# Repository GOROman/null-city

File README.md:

# NULL CITY NC-03

Bambu H3Cで製作する、交換式天板の6ボタンアーケードスティック。白い面取りケースに、NULL FONTのロゴとネイビー・マゼンタのデカールを組み合わせています。写真は2026-11-16の実機です。

**[ブラウザーで3Dプレビュー ↗](https://goroman.github.io/null-city/)** · [制作日記・設計記録](docs/development-diary.md) · [部品表](BOM.md)

## 仕様と構成

| 項目 | 内容 |
|---|---|
| 外形 | 公称300 × 190 mm、脚込み高さ約55 mm（レバー・ボタンを除く） |
| 筐体 | 下ケース・上フレーム・交換式天板。天板288 × 178 × 4 mm |
| レバー | セイミツ製のゲーセンバッグ実物に合わせた直接固定。40 × 40 mmピッチ、逃げ穴φ4.5 mm × 4 |
| ボタン | Blast City 1Pの6ボタン配列。メインφ30 × 6（緑3・透明3）、1P／STARTはφ24 |
| 表示LED | レバー8方向＋各ボタン、計16個の4 × 4 mm角窓。裏面にWS2812互換モジュール用受け座 |
| 筐体照明 | 前面・左右のLED収容溝と別体の乳白カバー |
| USB配線 | 背面ケーブル出口、外径4 mm想定のS字ガイドと押さえ |

実機写真で筐体・天板・操作部・デカールの組立を確認できます。レバーは試験片でねじ4本の固定と8方向動作を確認済み。通信、LED点灯、接続済み配線の干渉、耐久性は引き続き確認が必要です。写真だけで電気的な動作確認済みとはしていません。

## 製作データ

| 作りたいもの | データ・手順 |
|---|---|
| 本体一式 | [H3C用6プレート3MF](print/h3c/NC03_H3C_6plates_lighting_sliced.3mf) ／ [造形設定](PRINT_SETTINGS.md) |
| 天板 | [標準3MF](print/h3c/03_control_panel.3mf) ／ [時短試作3MF](print/h3c/03_control_panel_fast.3mf) |
| 表面マルチカラー天板 | [3MF](print/h3c/03_control_panel_multicolor_sliced.3mf) ／ [3色印刷・角LED窓の手順](print/h3c/PANEL_MULTICOLOR.md) |
| 下ケース・照明カバー | [下ケース時短3MF](print/h3c/01_lower_tray_fast.3mf) ／ [カバー3MF](print/h3c/06_light_diffusers.3mf) ／ [照明構成](LIGHTING.md) |
| デカール | [全4枚をA4一枚に配置したPDF](artwork/decal/NC03_all_decals_A4_versioned.pdf) ／ [印刷・Bambu Suiteカット手順](artwork/decal/README.md) |
| 部品の購入 | [機構BOM](BOM.md) ／ [CSV](BOM.csv) ／ [メーカー寸法図PDF](docs/references/README.md) |
| 嵌合確認 | [レバー取付・測定](docs/fit/README.md) ／ [照明試験片](print/lighting-fit/README.md) ／ [USBガイド試験片](print/usb-relief/README.md) |
| コントローラー基板 | [KiCad設計・回路図・電子部品BOM](hardware/nc03-controller/README.md) |
| NULL FONT | [フォントパッケージ](fonts/null-font/) ／ [ベクターロゴ](artwork/logo/null-city.svg) |

マルチカラー天板は凹ロゴの底面だけ白、`///`をマゼンタにする一体造形です。写真のデカール仕上げとは別の仕上げ方法で、3色印刷・LED保持は実物確認待ちです。

コントローラー基板はXIAO nRF52840 Plusを使うA0試作。USB／BLEの通信ファームウェア、Switch／PS互換性は未実装・未検証です。[基板の制約と対応範囲](hardware/nc03-controller/README.md)を確認してください。

## 3Dプリント

Bambu Studioの **H3C／0.4 mm Standard・Textured PEI Plate** を使用し、実際の材料と装着ノズルに合わせて再スライスします。

| 設定 | 本体の標準試作 | 同梱6プレート版の時短試作 |
|---|---|---|
| 積層／初層 | 0.20／0.20 mm | 0.28／0.20 mm |
| 壁 | 4周 | 3周 |
| 上面／底面 | 各5層 | 各4層 |
| 充填 | Gyroid 15% | Gyroid 10% |
| ブリム | 外周5 mm、隙間0.15 mm | 同左 |
| サポート | なし | なし |
| 外壁／天面 | 100／80 mm/s | 同左 |

PLAの開始値はノズル220℃、ベッド55℃、最大体積流量12 mm³/s。材料メーカーの指定を優先してください。脚は別プレートでTPU、カバーは半透明PLA。各専用ジョブの設定と見積は[PRINT_SETTINGS.md](PRINT_SETTINGS.md)を参照。

## デカールの印刷とカット

実機では天板・前面・左右の4枚を、[A4横一枚のベクターPDF](artwork/decal/NC03_all_decals_A4_versioned.pdf)から印刷しました。

- Canon XK130、A4写真用紙 光沢ゴールド（GL-101）、後トレイ、高品質・カラー・片面。
- 倍率100%、フチなしOFF、用紙に合わせるOFF。
- [Suite用カットデータ](artwork/decal/NC03_all_decals_A4_CUT_ONLY_NOMINAL.lac)は33穴＋4外周の計37閉輪郭。用紙を貼るたびにカメラで位置・角度を合わせます。
- 余白・塗り足しが必要な場合は[余白付きA4二枚版](artwork/decal/NC03_decals_A4_2sheets.pdf)を使用。

材料設定、刃、位置合わせと試し切りの注意点は[デカールREADME](artwork/decal/README.md)にまとめています。

## 設計図と3Dビューアー

[制作日記・設計記録](docs/development-diary.md)に、分解図・ワイヤーフレーム・照明構造・寸法・試作の経緯をまとめています。レンダリングの発光表現は完成イメージです。

[PBR Webビューアー](https://goroman.github.io/null-city/)では回転・ズーム・分解表示、HDR IBL、SSAO、露出・背景色、RGB LEDアニメーション、レバーとボタンの操作を試せます。[ローカル実行・GitHub Pages公開手順](web/README.md)。

## モデルと画像の再生成

`NULL_CITY_NC03.blend` が組立モデル、`NULL_CITY_NC03.py` が生成スクリプト、`STL/` が部品別の造形データです。リポジトリ直下で実行します。

```sh
blender --background --factory-startup --python-exit-code 1 --python NULL_CITY_NC03.py
python3 scripts/render_all.py
```

実機のトップ写真は `docs/images/nc03-built.jpg`。Blenderの再レンダリングでは更新されません。照明・デカールなどの生成手順は各リンク先を参照してください。

## ライセンス

Copyright © 2026 GOROman。適用範囲は[LICENSE](LICENSE)を参照。

| 対象 | ライセンス |
|---|---|
| スクリプト（フォントパッケージを除く） | [MIT](LICENSES/MIT.txt) |
| 造形・デカール・オリジナル画像・設計設定・ドキュメント | [CC BY 4.0](LICENSES/CC-BY-4.0.txt) |
| NULL FONT（字形ソース・生成スクリプトを含む） | [SIL OFL 1.1](fonts/null-font/OFL.txt) |

メーカー寸法図など第三者資料は、それぞれの権利・ライセンスに従います。

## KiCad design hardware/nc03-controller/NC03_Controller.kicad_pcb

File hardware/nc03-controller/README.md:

# NC-03 USB/BLE controller — KiCad A0

XIAO nRF52840 **Plus / non-Sense**を使う、NC-03用キャリア基板の試作設計です。**基板データは作成済み、実装・通信ファームウェア・実機互換性・ケース内取付は未検証**です。Switch/PSで動作する完成済みコントローラーではありません。

[KiCadプロジェクト](NC03_Controller.kicad_pro) / [回路図PDF](docs/schematic.pdf) / [基板表面](docs/board-top.svg) / [基板裏面](docs/board-bottom.svg) / [実装図](docs/assembly.svg) / [部品表CSV](BOM.csv) / [ピン割当](firmware/pinmap.csv) / [一次資料](docs/REFERENCES.md)

KiCadからの実データ描画。U1のXIAO本体は3Dモデル未収録のため描画されません。U1の29パッドと実装位置は基板図で確認できます。形状・配線の画像であり、通電写真ではありません。

## 現行天板のシリアルLED

新しい[四角窓・シリアルLED天板](../../print/h3c/PANEL_MULTICOLOR.md)では、16個のNeoPixel/WS2812互換モジュールと前面・側面ストリップをJ14から1本の直列チェーンで制御します。基板の配線変更は不要です。全ピクセルを含めてRGB電流予算150mAを分配します。A0のPCA9685・R41〜R56・J12/J13は旧単色構成用のオプションとなり、新LEDのDINには接続しません。

下表・回路図・基板BOMは旧単色ドライバーも搭載できるA0の共通回路を示します。現行天板でその部品は省略可能です。通信・LEDファームと新モジュール装着は未検証です。

## 構成

| 機能 | 回路・状態 |
|---|---|
| MCU | XIAO nRF52840 Plus、標準版/Senseは代用不可。Plus底面パッドも接合 |
| 主入力 | レバー4方向＋主6＋1P/STARTの12点をGPIO直結、330Ω＋1nF、外部10kプルアップ |
| 操作表示 | 既存の3mm単色LED16個、PCA9685PWで個別PWM、1kΩ抵抗で約2〜3mA/点 |
| 前面・左右RGB | 5VのWS2812系ストリップ用出力、3.3→5Vレベル変換、ストリップを直列に接続 |
| LED電源 | USB VBUS→350mA PTC→TPS22918。起動時OFF、USB設定完了後に予算内で有効化 |
| バッテリー | 保護回路付き1S LiPo、XIAO内蔵充電回路を利用。逆接保護・独立電源パスはキャリアに追加していない |
| モード | 外付けSPDT ON–OFF–ONでPC／PS外部変換器／Switch、別SPSTでUSB／BLE |
| USB | XIAOのType-Cを利用。キャリアに2個目のUSB端子やUSB信号配線は設けない |
| 拡張 | SWD、3.3V I²C。Home/Share/Touchpad等の補助入力基板は未設計 |
| 基板 | 110×85mm、2層、1.6mm想定、M3用φ3.2 NPTH×4、ピッチ100×75mm |

## 接続先と切り替え

| 選択 | 接続計画 | 実装状況 |
|---|---|---|
| PC＋USB | USB HIDゲームパッド、1msポーリング目標 | ハード回路のみ。ファーム未実装、遅延未測定 |
| PC＋BLE | HID over GATT、接続間隔7.5msを要求 | 同上。ホストによって実際の間隔が変わる |
| Switch＋USB | 初代Switch向けUSBプロトコル | ファーム未実装、実機未検証。Switch 2を含まない |
| PS＋USB | 対応する市販認証変換器へUSB接続 | 変換器・PS世代・USBプロファイルは選定/実機照合待ち。直結対応ではない |
| Switch/PS＋BLE | 対象外 | BLE搭載だけでは両コンソールの無線仕様に対応しない |

J10は**PC–PS/ADAPTER–SWITCH**の並びになる3位置スイッチです。共通GND、両端の信号を別々に読むので、中立OFF位置でも電源は落ちません。未接続はPS/ADAPTER位置になります。USB/BLEは別スイッチに分け、J11開放=USB、短絡=BLE。切り替え後は全入力解除→通信停止→USB再列挙またはBLE接続を行うファーム仕様です。[詳細](firmware/PROTOCOL.md)

PS4/PS5は認証のある対応変換器などが必要です。例としてBrookの公開資料を参照していますが、この自作デバイスは互換リストに載っておらず、変換器経由の動作も確認していません。USBの識別子だけでPS対応とはしません。PS世代の回答後に対象変換器を確定します。

## コネクター

全コネクターは上面実装のJST XH縦型2.50mm。**ピン番号は基板図の四角パッドを1番**として読む。一般的なLiPoのJST PHとは異なり、極性も共通規格と仮定しないこと。

| 端子 | ピン順 |
|---|---|
| J1 レバー | 1 GND、2 UP、3 DOWN、4 LEFT、5 RIGHT |
| J2〜J7 主ボタン | B1〜B6、各1 GND／2入力 |
| J8・J9 補助ボタン | 1P／START、各1 GND／2入力 |
| J10 プロファイル | 1 PC側、2共通GND、3 Switch側。SPDT ON–OFF–ON |
| J11 USB/BLE | 1選択入力、2 GND。開放USB、短絡BLE |
| J12 方向LED | 1 +5V_LED、2〜9はK0〜K7、共通アノード配線。方向は前面から0=右、以降反時計回り45°刻み |
| J13 ボタンLED | 1 +5V_LED、2〜9はK8〜K15、B1〜B6・1P・STARTの順 |
| J14 RGB | 1 +5V_LED、2 DIN、3 GND。ストリップの入力側へ |
| J15 電池 | 1保護済み電池＋、2電池−/GND。1S 3.7V公称／満充電4.2Vのみ |
| J16 電池スイッチ | 1電池＋、2 XIAO BAT＋。外付けSPSTで結ぶ。OFFでは電池を充電回路からも切り離す |
| J17 AUX | 1 3.3V、2 SDA、3 SCL、4 GND。5V機器用ではない |
| J18 SWD | 1 3.3V参照、2 SWDIO、3 SWDCLK、4 RESET、5 GND |

LS-55-01のハーネスの実際の方向・共通線は現物照合し、線色で決めない。GPIOへ5VやLED電源を接続しない。XIAO標準11 GPIOのキャリアとしては動作しない。

## 電源とケースへの組付け

USBと電池はXIAOの既存回路へ接続します。別の5V電源をJ14やVBUSへ注入しません。主電源はXIAO、キャリアの3.3Vは出力から受けるだけです。電池の保護回路・適切な充電設定は別途必要。J16をOFFにすると電池充電も止まります。

RGBの合計はソフトで150mAを初期上限にし、単色LED約50mA、MCU/無線、電池充電の最大電流を加えて実際に許可されたUSB電流を下回る必要があります。350mA PTCは精密な定電流制限ではありません。TPS22918の立ち上がりと47uFの充電突入は実測します。PCA9685の出力はリセット時LOWのため、全消灯を書いてからLED_ENABLEを上げます。電池駆動時は5V昇圧がないためLEDを消灯します。

USB Type-Cを外側に出す場合は、XIAOのUSB-Cにつながるデータ対応パネル延長部品をケースに固定します。**既存の背面8×6mm切り欠きはケーブル用であり、Type-Cメス端子のパネル固定穴ではありません。** 端子外形、CC/USB2.0配線とケーブル方向を現物照合したうえで、後から別ブラケット・開口を設計します。この変更で印刷中の下ケース/STL/3MFは変更していません。

基板のM3穴ピッチ100×75mmは独立した新設穴で、現行ケースのボスと一致しません。**ケースとの機械的適合は未完了**です。発注前に1:1基板図を印刷し、レバー本体・ボタン端子・ナット・USB S字ガイド・LED溝を避けて仮置きします。M3絶縁スペーサー等の取付台とType-C固定は次の機械設計。アンテナ側はcarrier銅箔禁止領域を確保しましたが、筐体内の金属レバー・配線・電池からの離隔とRF性能は実物評価が必要です。

## 検証と再生成

KiCad 10.0.8でERC、DRC、回路図とPCBのネット/フットプリント照合を実施。結果は[ERC](checks/ERC.rpt)／[DRC](checks/DRC.rpt)。配線済みデータが正本です。自動配線後に0.2mm未満のネック部分を0.2mmへ拡幅し、改めてDRCしています。

再生成は現在の基板配線を上書きします。通常の閲覧・編集は `NC03_Controller.kicad_pro` を開きます。生成スクリプトと詳細手順は[scripts/README.md](scripts/README.md)。

製造用Gerber/ドリルは含めていません。通信ファーム、PS変換器、ケース取付、充電電流・ESD・RF・遅延を確認してから製造リリースに進みます。ERC/DRC合格は、これらの実機検証の代わりにはなりません。

## 追加購入部品

[電子部品BOM](BOM.csv)は基板上89部品。ほかにXHハウジング/コンタクトとハーネス、外付けSPDT ON–OFF–ON×1、SPST×2（USB/BLEと電池）、データ対応USB-Cパネル延長、適切な保護付き1S電池、RGBストリップ、現行天板用の9.1mm角シリアルRGBモジュール16個（旧丸窓天板のみ3mm単色LED）、M3取付部品が必要です。XIAO本体はU1としてBOMに含みます。ストリップ長、電池サイズ、PS変換器は未確定です。

ソフトウェアはMIT。Seeedのランドパターンを組み込むPCB/回路図と派生出力はCC BY-SA 4.0。[出典・変更点・例外](vendor/README.md)。筐体・デカールのCC BY 4.0とNULL FONTのOFLは変更していません。

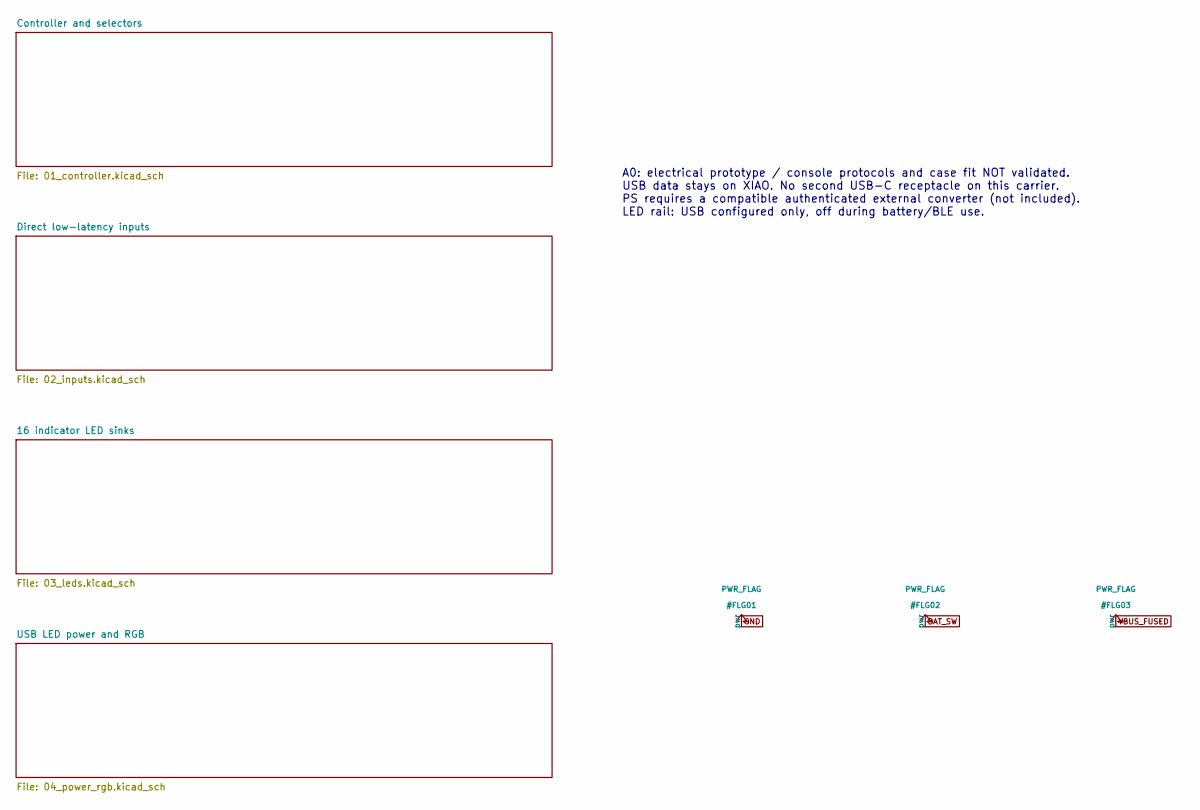
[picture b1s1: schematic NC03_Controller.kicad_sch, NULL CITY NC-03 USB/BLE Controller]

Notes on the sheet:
A0: electrical prototype / console protocols and case fit NOT validated. USB data stays on XIAO. No second USB-C receptacle on this carrier. PS requires a compatible authenticated external converter (not included). LED rail: USB configured only, off during battery/BLE use.

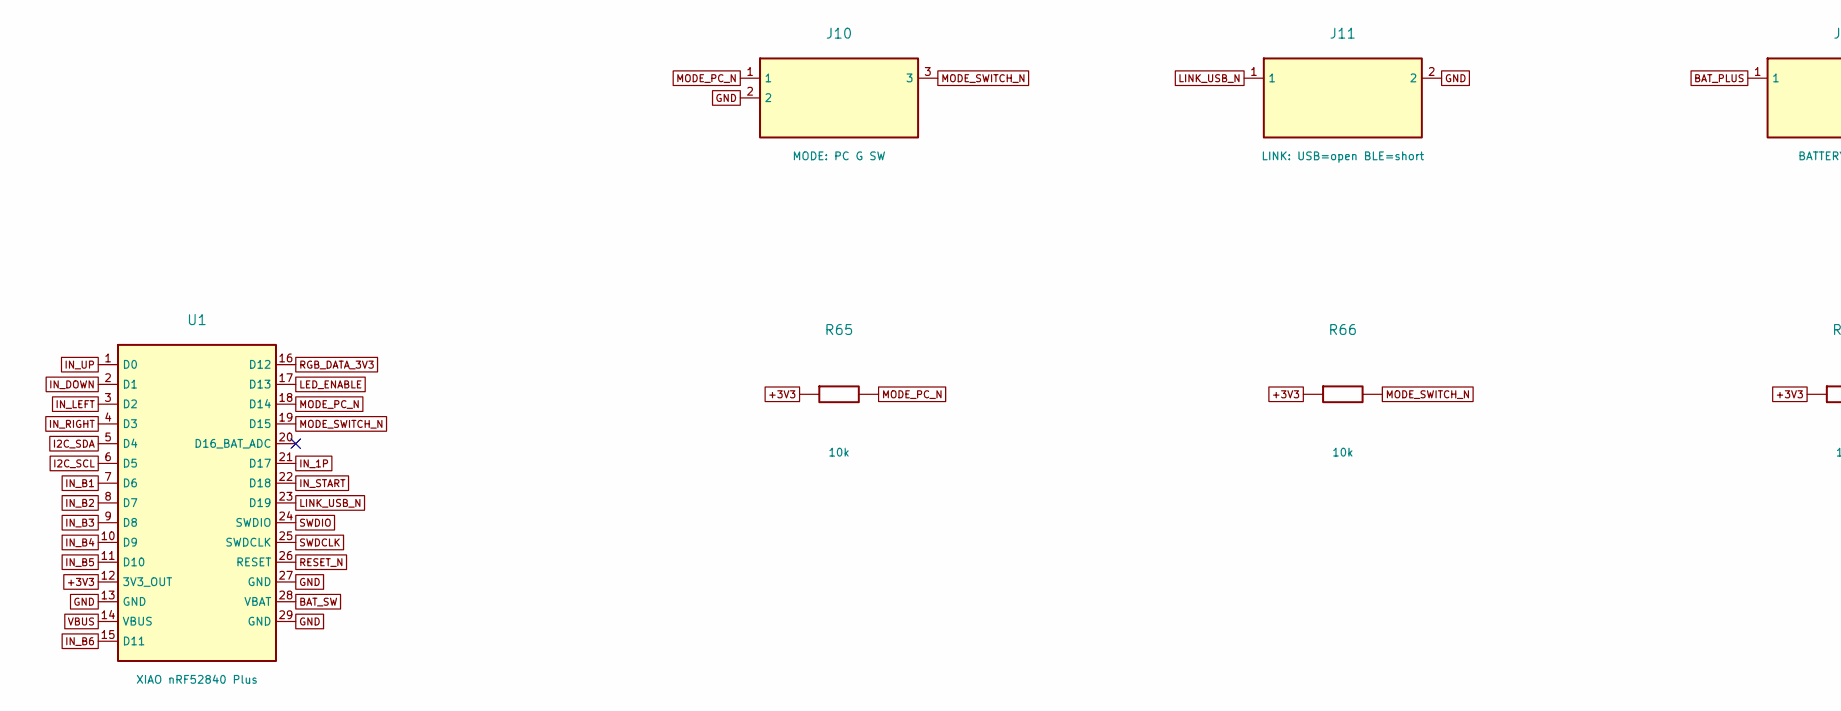
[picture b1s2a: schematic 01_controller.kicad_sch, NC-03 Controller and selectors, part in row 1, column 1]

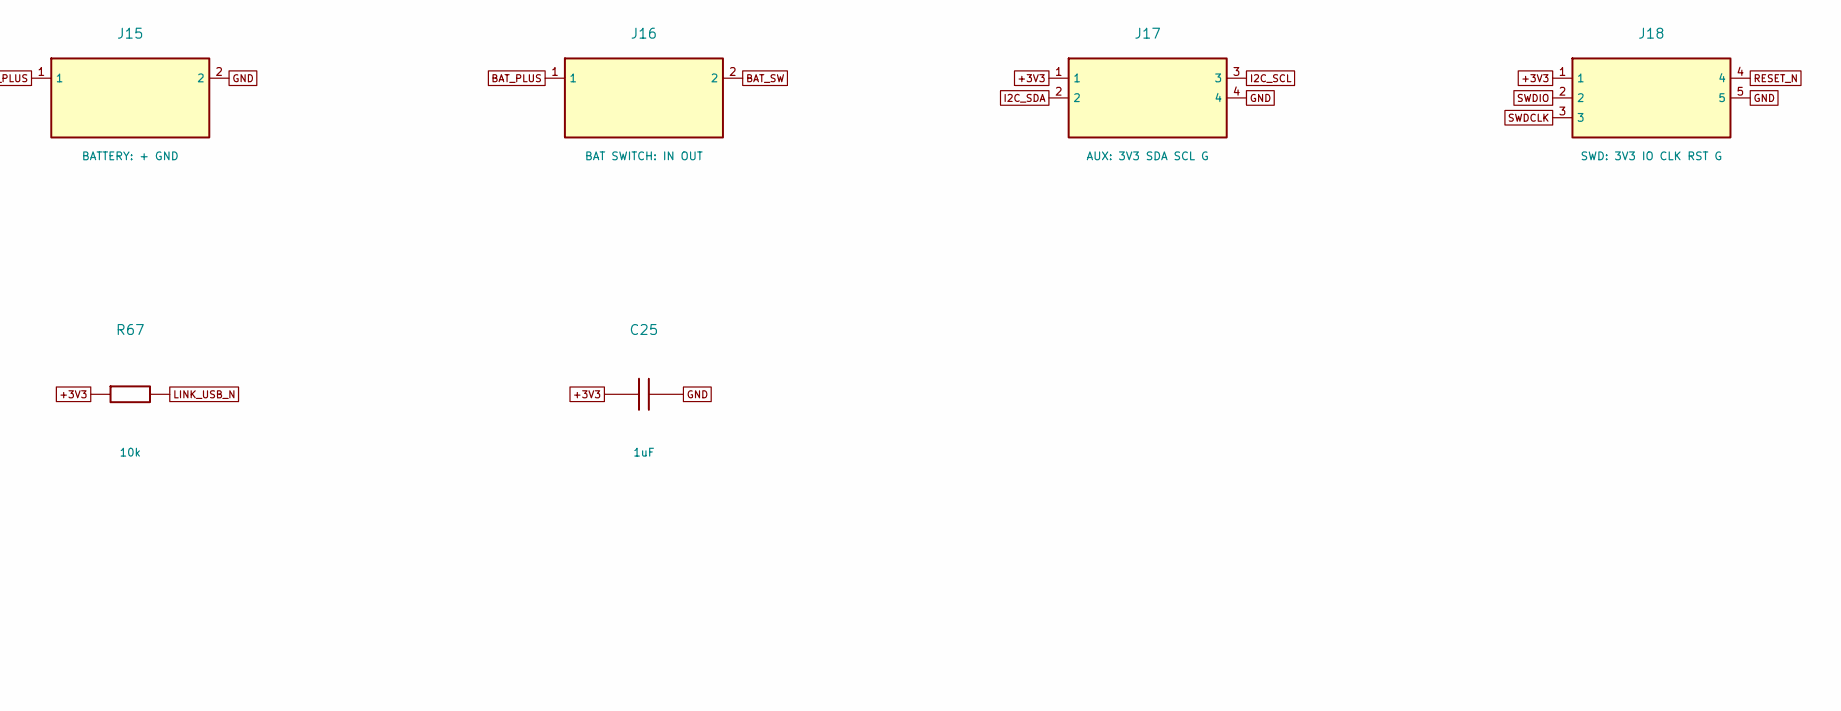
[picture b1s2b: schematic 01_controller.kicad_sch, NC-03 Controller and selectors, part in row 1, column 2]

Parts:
C25: 1uF; Capacitor_SMD_C_0805_2012Metric
J10: MODE: PC G SW; Connector_JST_JST_XH_B3B-XH-A_1x03_P2.50mm_Vertical
J11: LINK: USB=open BLE=short; Connector_JST_JST_XH_B2B-XH-A_1x02_P2.50mm_Vertical
J15: BATTERY: + GND; Connector_JST_JST_XH_B2B-XH-A_1x02_P2.50mm_Vertical
J16: BAT SWITCH: IN OUT; Connector_JST_JST_XH_B2B-XH-A_1x02_P2.50mm_Vertical
J17: AUX: 3V3 SDA SCL G; Connector_JST_JST_XH_B4B-XH-A_1x04_P2.50mm_Vertical
J18: SWD: 3V3 IO CLK RST G; Connector_JST_JST_XH_B5B-XH-A_1x05_P2.50mm_Vertical
R65, R66, R67: 10k; Resistor_SMD_R_0805_2012Metric
U1: XIAO nRF52840 Plus; XIAO_nRF52840_Plus

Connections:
+3V3: C25.1, J17.1, J18.1, R65.1, R66.1, R67.1, U1.12 (3V3_OUT); also elsewhere on the board
BAT_PLUS: J15.1, J16.1
BAT_SW: J16.2, U1.28 (VBAT)
GND: C25.2, J10.2, J11.2, J15.2, J17.4, J18.5, U1.13 (GND), U1.27 (GND), U1.29 (GND); also elsewhere on the board
I2C_SCL: J17.3, U1.6 (D5); also elsewhere on the board
I2C_SDA: J17.2, U1.5 (D4); also elsewhere on the board
IN_1P: U1.21 (D17); also elsewhere on the board
IN_B1: U1.7 (D6); also elsewhere on the board
IN_B2: U1.8 (D7); also elsewhere on the board
IN_B3: U1.9 (D8); also elsewhere on the board
IN_B4: U1.10 (D9); also elsewhere on the board
IN_B5: U1.11 (D10); also elsewhere on the board
IN_B6: U1.15 (D11); also elsewhere on the board
IN_DOWN: U1.2 (D1); also elsewhere on the board
IN_LEFT: U1.3 (D2); also elsewhere on the board
IN_RIGHT: U1.4 (D3); also elsewhere on the board
IN_START: U1.22 (D18); also elsewhere on the board
IN_UP: U1.1 (D0); also elsewhere on the board
LED_ENABLE: U1.17 (D13); also elsewhere on the board
LINK_USB_N: J11.1, R67.2, U1.23 (D19)
MODE_PC_N: J10.1, R65.2, U1.18 (D14)
MODE_SWITCH_N: J10.3, R66.2, U1.19 (D15)
RESET_N: J18.4, U1.26 (RESET)
RGB_DATA_3V3: U1.16 (D12); also elsewhere on the board
SWDCLK: J18.3, U1.25 (SWDCLK)
SWDIO: J18.2, U1.24 (SWDIO)
VBUS: U1.14 (VBUS); also elsewhere on the board

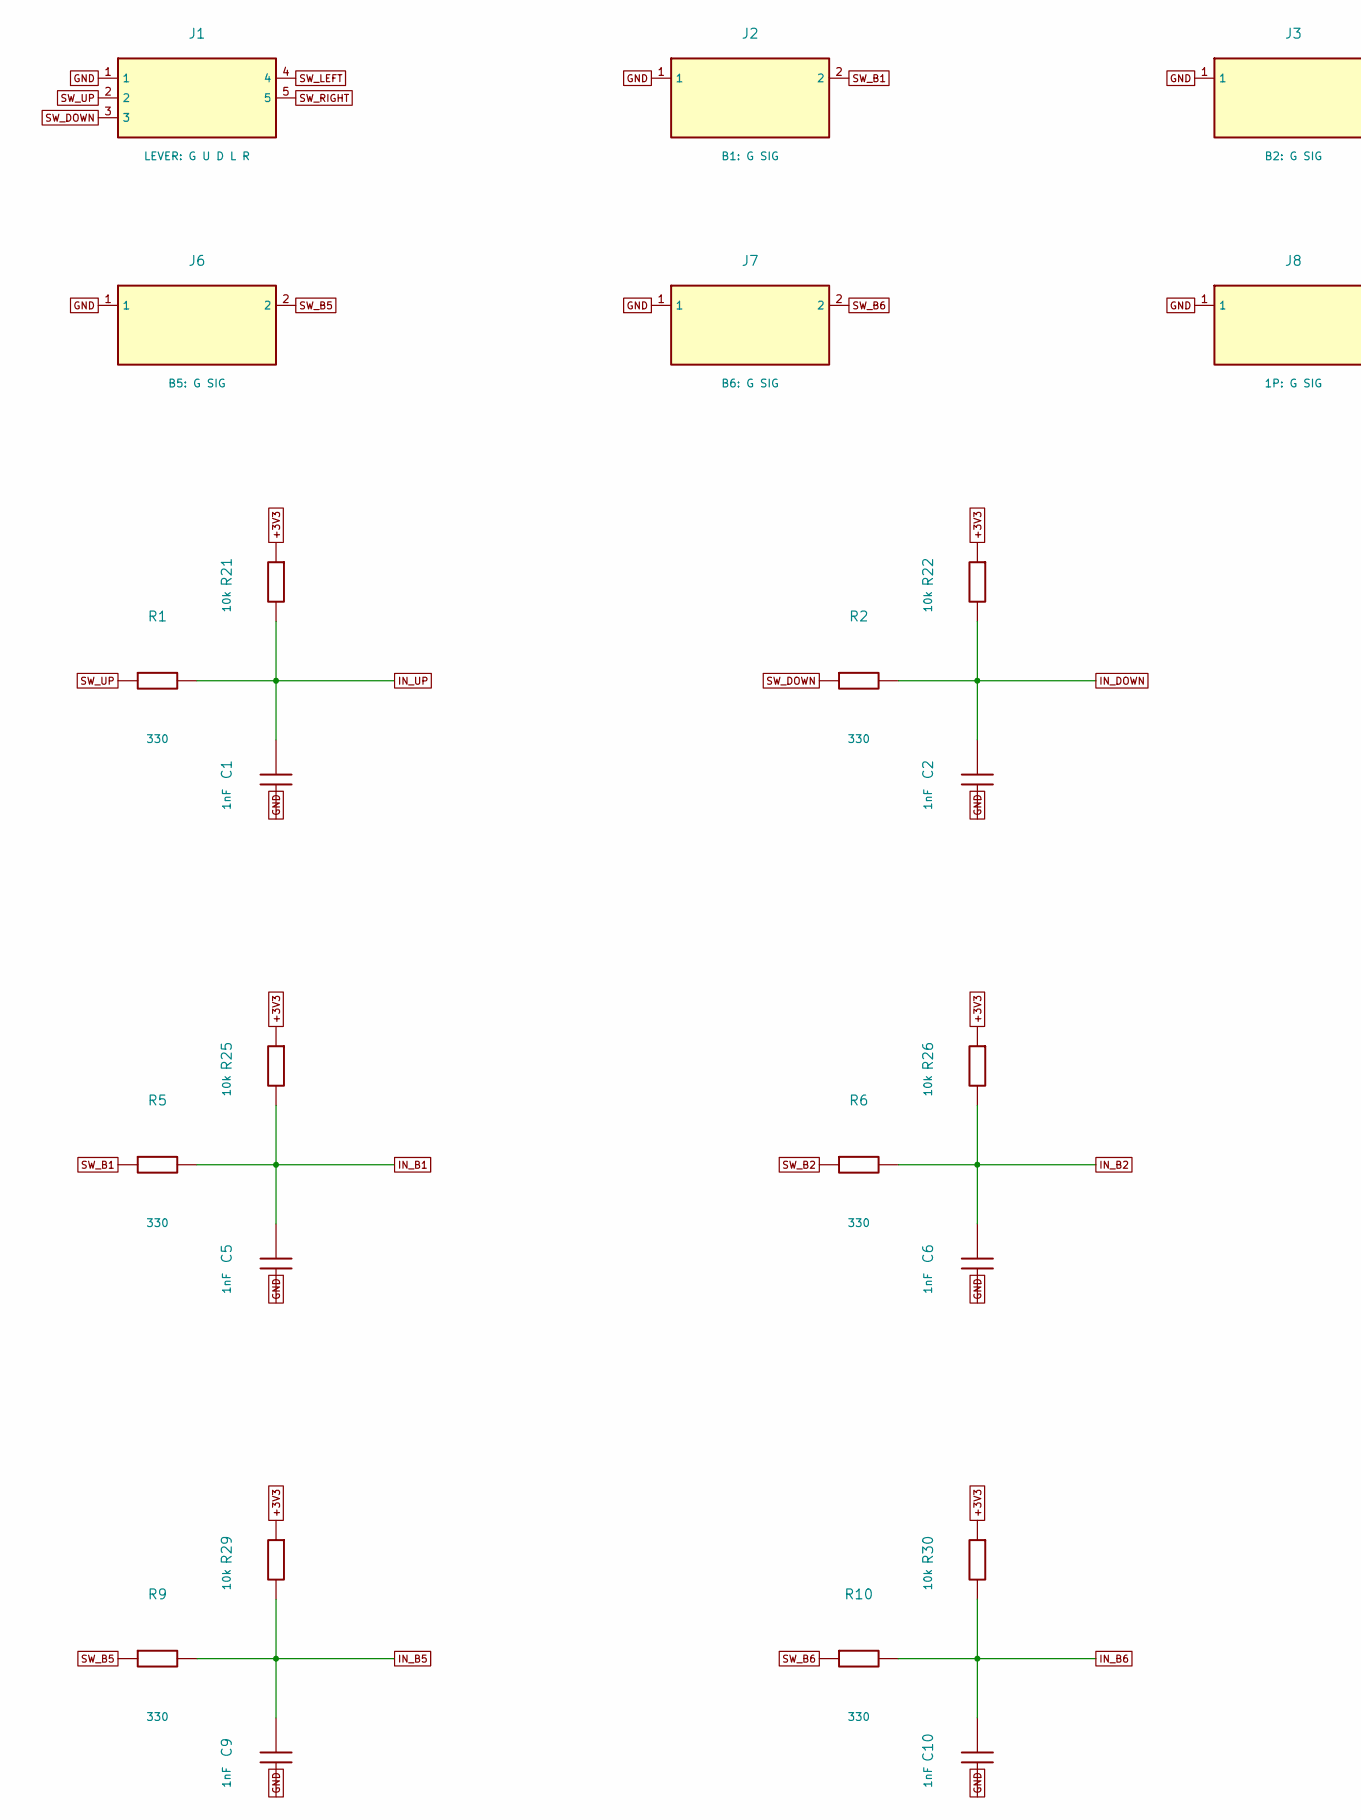
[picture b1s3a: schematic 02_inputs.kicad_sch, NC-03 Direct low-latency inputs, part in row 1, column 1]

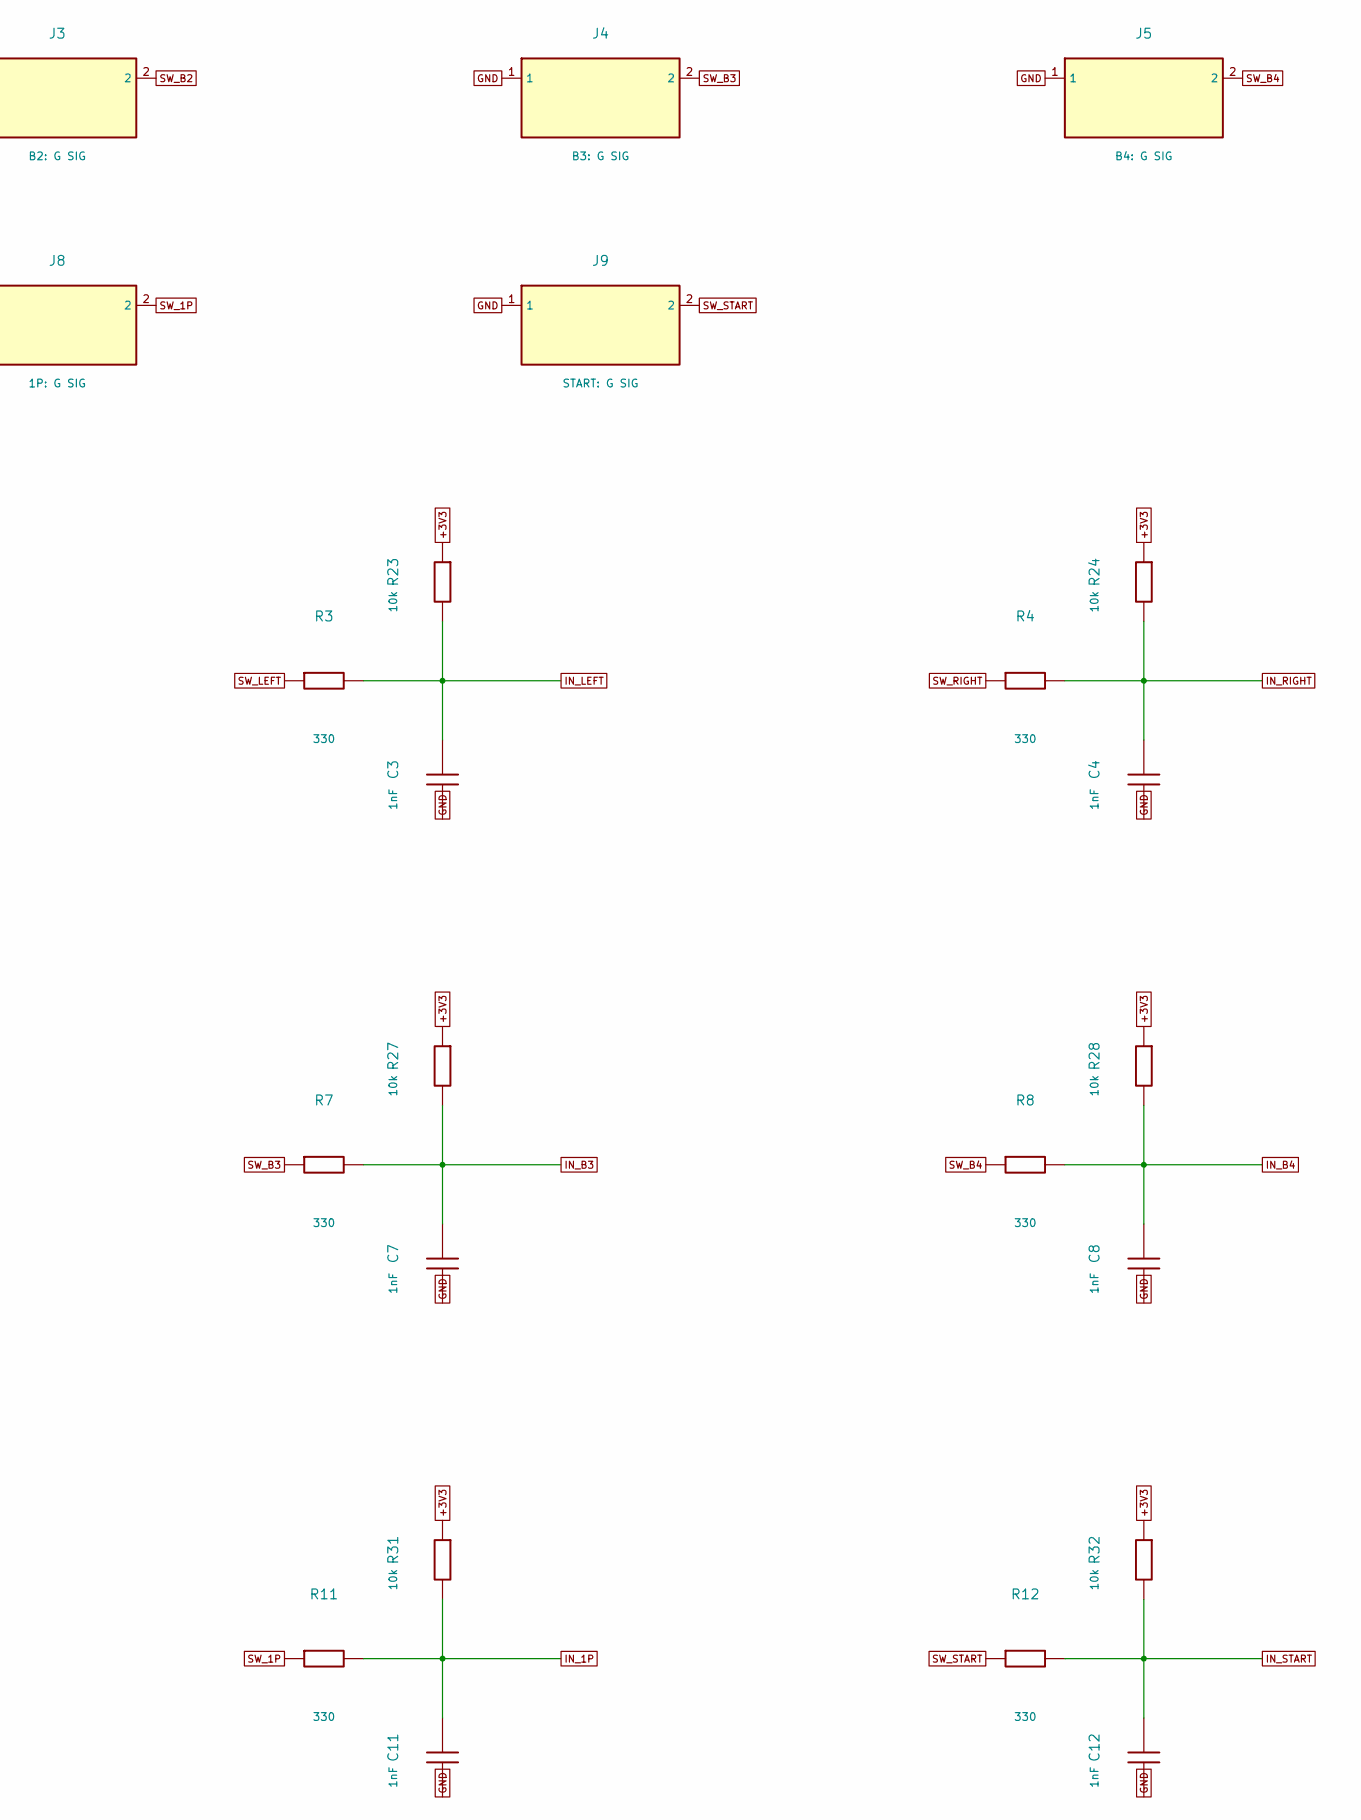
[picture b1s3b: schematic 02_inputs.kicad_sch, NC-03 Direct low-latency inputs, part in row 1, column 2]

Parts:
C1, C2, C3, C4, C5, C6, C7, C8, C9, C10, C11, C12: 1nF; Capacitor_SMD_C_0805_2012Metric
J1: LEVER: G U D L R; Connector_JST_JST_XH_B5B-XH-A_1x05_P2.50mm_Vertical
J2: B1: G SIG; Connector_JST_JST_XH_B2B-XH-A_1x02_P2.50mm_Vertical
J3: B2: G SIG; Connector_JST_JST_XH_B2B-XH-A_1x02_P2.50mm_Vertical
J4: B3: G SIG; Connector_JST_JST_XH_B2B-XH-A_1x02_P2.50mm_Vertical
J5: B4: G SIG; Connector_JST_JST_XH_B2B-XH-A_1x02_P2.50mm_Vertical
J6: B5: G SIG; Connector_JST_JST_XH_B2B-XH-A_1x02_P2.50mm_Vertical
J7: B6: G SIG; Connector_JST_JST_XH_B2B-XH-A_1x02_P2.50mm_Vertical
J8: 1P: G SIG; Connector_JST_JST_XH_B2B-XH-A_1x02_P2.50mm_Vertical
J9: START: G SIG; Connector_JST_JST_XH_B2B-XH-A_1x02_P2.50mm_Vertical
R1, R2, R3, R4, R5, R6, R7, R8, R9, R10, R11, R12: 330; Resistor_SMD_R_0805_2012Metric
R21, R22, R23, R24, R25, R26, R27, R28, R29, R30, R31, R32: 10k; Resistor_SMD_R_0805_2012Metric

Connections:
+3V3: R21.1, R22.1, R23.1, R24.1, R25.1, R26.1, R27.1, R28.1, R29.1, R30.1, R31.1, R32.1; also elsewhere on the board
GND: C1.2, C2.2, C3.2, C4.2, C5.2, C6.2, C7.2, C8.2, C9.2, C10.2, C11.2, C12.2, J1.1, J2.1, J3.1, J4.1, J5.1, J6.1, J7.1, J8.1, J9.1; also elsewhere on the board
IN_1P: C11.1, R11.2, R31.2; also elsewhere on the board
IN_B1: C5.1, R5.2, R25.2; also elsewhere on the board
IN_B2: C6.1, R6.2, R26.2; also elsewhere on the board
IN_B3: C7.1, R7.2, R27.2; also elsewhere on the board
IN_B4: C8.1, R8.2, R28.2; also elsewhere on the board
IN_B5: C9.1, R9.2, R29.2; also elsewhere on the board
IN_B6: C10.1, R10.2, R30.2; also elsewhere on the board
IN_DOWN: C2.1, R2.2, R22.2; also elsewhere on the board
IN_LEFT: C3.1, R3.2, R23.2; also elsewhere on the board
IN_RIGHT: C4.1, R4.2, R24.2; also elsewhere on the board
IN_START: C12.1, R12.2, R32.2; also elsewhere on the board
IN_UP: C1.1, R1.2, R21.2; also elsewhere on the board
SW_1P: J8.2, R11.1
SW_B1: J2.2, R5.1
SW_B2: J3.2, R6.1
SW_B3: J4.2, R7.1
SW_B4: J5.2, R8.1
SW_B5: J6.2, R9.1
SW_B6: J7.2, R10.1
SW_DOWN: J1.3, R2.1
SW_LEFT: J1.4, R3.1
SW_RIGHT: J1.5, R4.1
SW_START: J9.2, R12.1
SW_UP: J1.2, R1.1

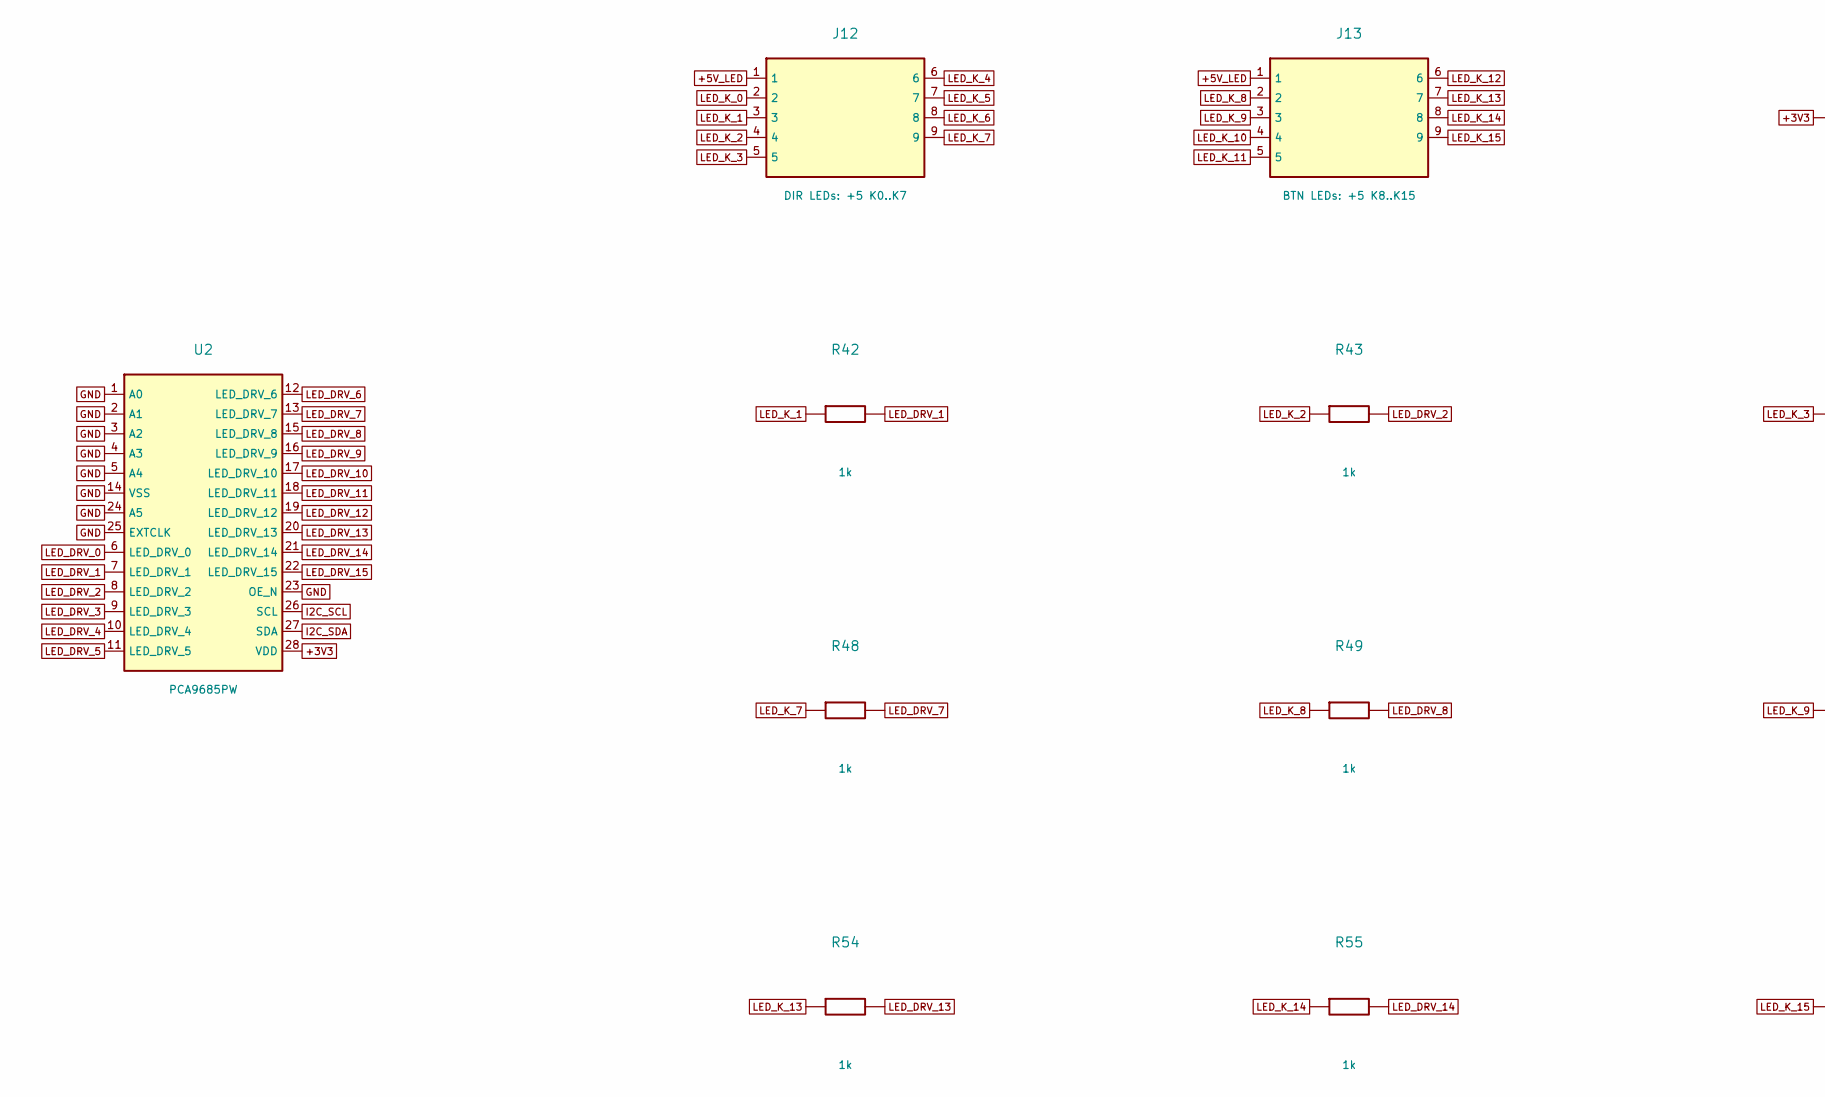
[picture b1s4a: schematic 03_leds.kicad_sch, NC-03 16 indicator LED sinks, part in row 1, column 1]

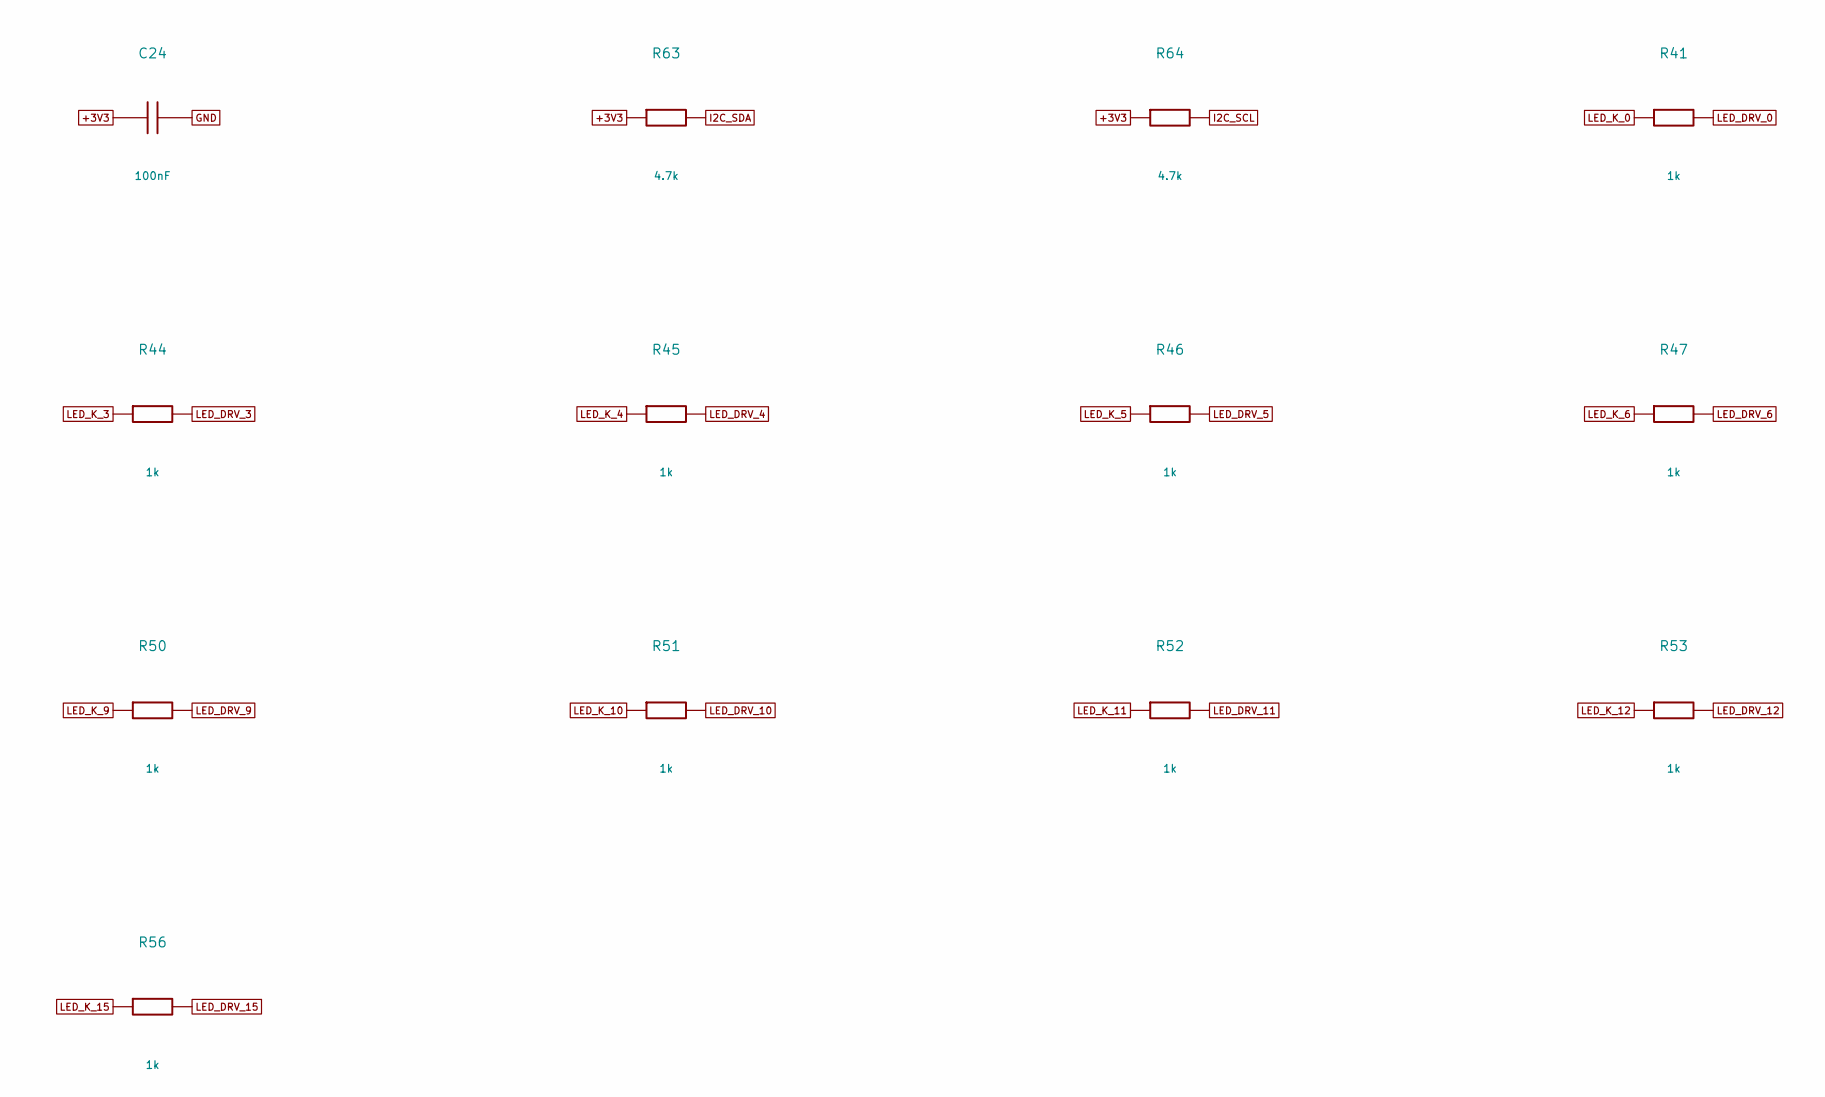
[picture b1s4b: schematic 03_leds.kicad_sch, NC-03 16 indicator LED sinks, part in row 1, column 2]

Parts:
C24: 100nF; Capacitor_SMD_C_0805_2012Metric
J12: DIR LEDs: +5 K0..K7; Connector_JST_JST_XH_B9B-XH-A_1x09_P2.50mm_Vertical
J13: BTN LEDs: +5 K8..K15; Connector_JST_JST_XH_B9B-XH-A_1x09_P2.50mm_Vertical
R41, R42, R43, R44, R45, R46, R47, R48, R49, R50, R51, R52, R53, R54, R55, R56: 1k; Resistor_SMD_R_0805_2012Metric
R63, R64: 4.7k; Resistor_SMD_R_0805_2012Metric
U2: PCA9685PW; Package_SO_TSSOP-28_4.4x9.7mm_P0.65mm

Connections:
+3V3: C24.1, R63.1, R64.1, U2.28 (VDD); also elsewhere on the board
+5V_LED: J12.1, J13.1; also elsewhere on the board
GND: C24.2, U2.1 (A0), U2.2 (A1), U2.3 (A2), U2.4 (A3), U2.5 (A4), U2.14 (VSS), U2.23 (OE_N), U2.24 (A5), U2.25 (EXTCLK); also elsewhere on the board
I2C_SCL: R64.2, U2.26 (SCL); also elsewhere on the board
I2C_SDA: R63.2, U2.27 (SDA); also elsewhere on the board
LED_DRV_0: R41.2, U2.6 (LED_DRV_0)
LED_DRV_1: R42.2, U2.7 (LED_DRV_1)
LED_DRV_2: R43.2, U2.8 (LED_DRV_2)
LED_DRV_3: R44.2, U2.9 (LED_DRV_3)
LED_DRV_4: R45.2, U2.10 (LED_DRV_4)
LED_DRV_5: R46.2, U2.11 (LED_DRV_5)
LED_DRV_6: R47.2, U2.12 (LED_DRV_6)
LED_DRV_7: R48.2, U2.13 (LED_DRV_7)
LED_DRV_8: R49.2, U2.15 (LED_DRV_8)
LED_DRV_9: R50.2, U2.16 (LED_DRV_9)
LED_DRV_10: R51.2, U2.17 (LED_DRV_10)
LED_DRV_11: R52.2, U2.18 (LED_DRV_11)
LED_DRV_12: R53.2, U2.19 (LED_DRV_12)
LED_DRV_13: R54.2, U2.20 (LED_DRV_13)
LED_DRV_14: R55.2, U2.21 (LED_DRV_14)
LED_DRV_15: R56.2, U2.22 (LED_DRV_15)
LED_K_0: J12.2, R41.1
LED_K_1: J12.3, R42.1
LED_K_2: J12.4, R43.1
LED_K_3: J12.5, R44.1
LED_K_4: J12.6, R45.1
LED_K_5: J12.7, R46.1
LED_K_6: J12.8, R47.1
LED_K_7: J12.9, R48.1
LED_K_8: J13.2, R49.1
LED_K_9: J13.3, R50.1
LED_K_10: J13.4, R51.1
LED_K_11: J13.5, R52.1
LED_K_12: J13.6, R53.1
LED_K_13: J13.7, R54.1
LED_K_14: J13.8, R55.1
LED_K_15: J13.9, R56.1

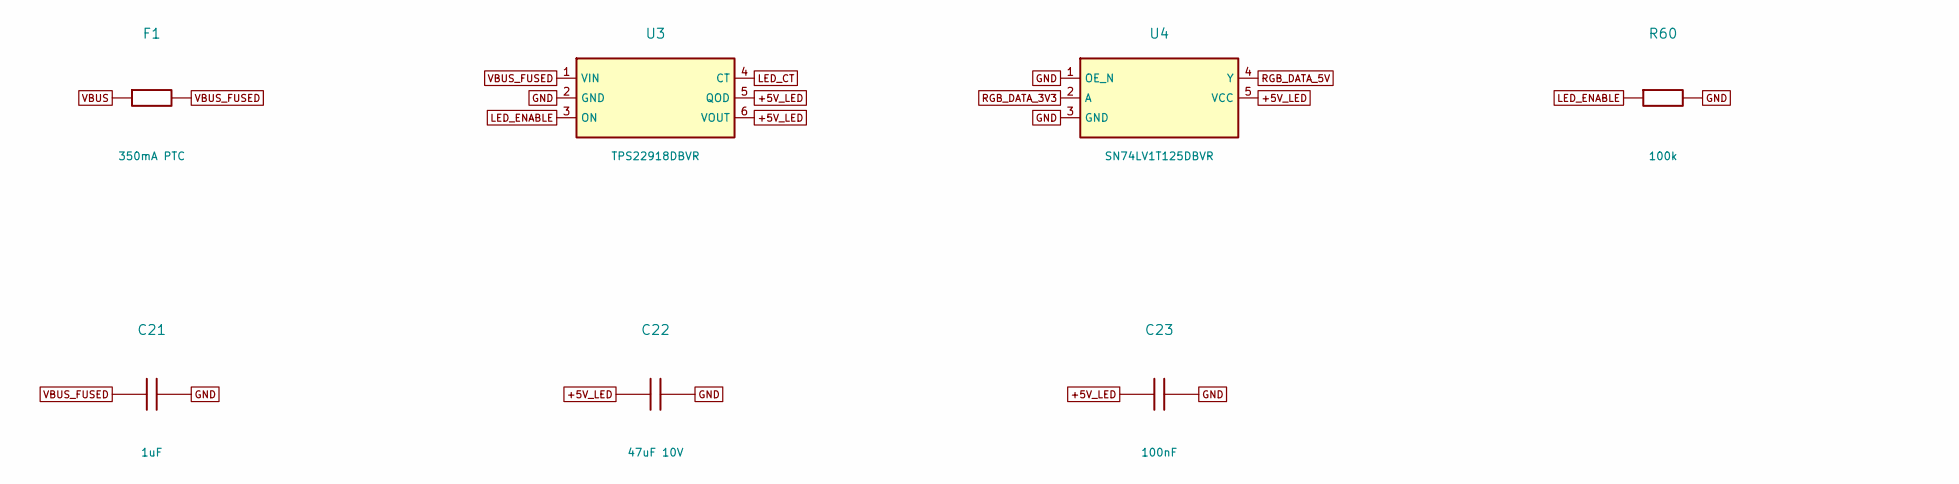
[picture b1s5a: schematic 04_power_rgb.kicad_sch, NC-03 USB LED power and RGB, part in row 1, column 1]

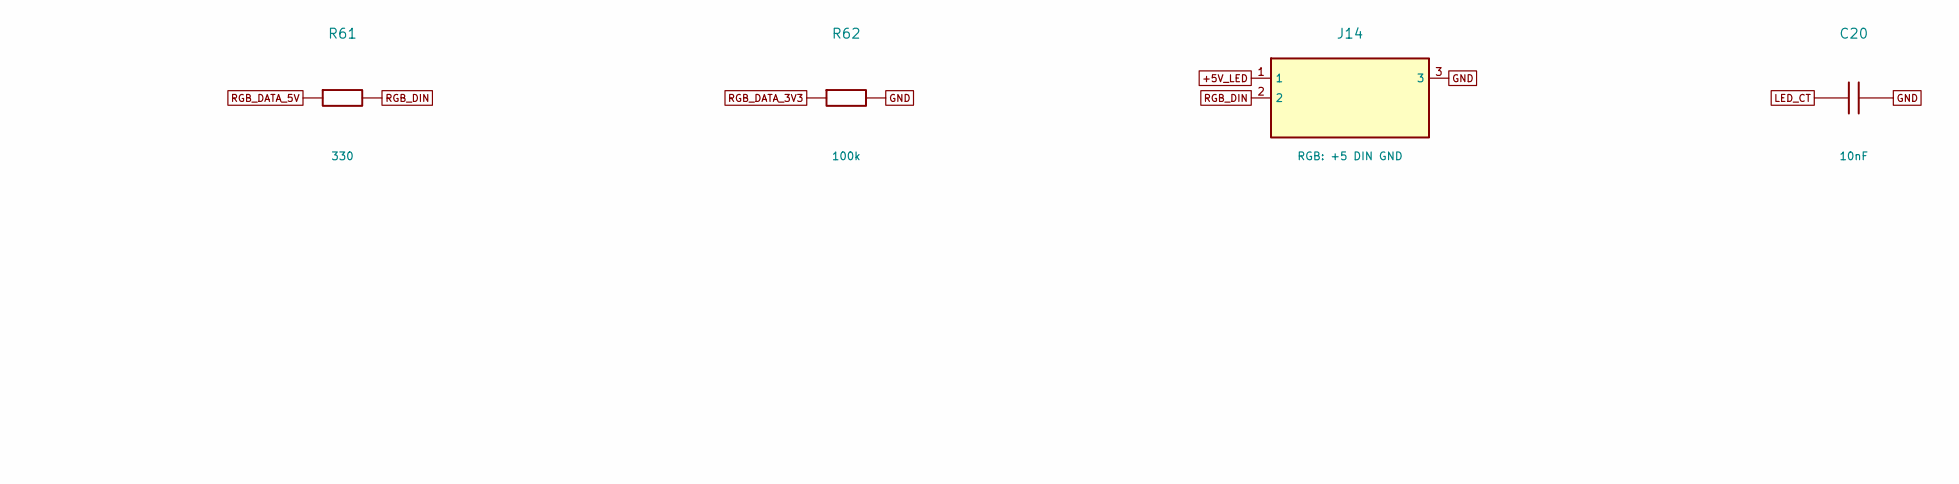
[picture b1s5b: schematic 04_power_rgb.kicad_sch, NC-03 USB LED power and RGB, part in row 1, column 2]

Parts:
C20: 10nF; Capacitor_SMD_C_0805_2012Metric
C21: 1uF; Capacitor_SMD_C_0805_2012Metric
C22: 47uF 10V; Capacitor_SMD_C_0805_2012Metric
C23: 100nF; Capacitor_SMD_C_0805_2012Metric
F1: 350mA PTC; Fuse_Fuse_1206_3216Metric
J14: RGB: +5 DIN GND; Connector_JST_JST_XH_B3B-XH-A_1x03_P2.50mm_Vertical
R60, R62: 100k; Resistor_SMD_R_0805_2012Metric
R61: 330; Resistor_SMD_R_0805_2012Metric
U3: TPS22918DBVR; Package_TO_SOT_SMD_SOT-23-6
U4: SN74LV1T125DBVR; Package_TO_SOT_SMD_SOT-23-5

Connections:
+5V_LED: C22.1, C23.1, J14.1, U3.5 (QOD), U3.6 (VOUT), U4.5 (VCC); also elsewhere on the board
GND: C20.2, C21.2, C22.2, C23.2, J14.3, R60.2, R62.2, U3.2 (GND), U4.1 (OE_N), U4.3 (GND); also elsewhere on the board
LED_CT: C20.1, U3.4 (CT)
LED_ENABLE: R60.1, U3.3 (ON); also elsewhere on the board
RGB_DATA_3V3: R62.1, U4.2 (A); also elsewhere on the board
RGB_DATA_5V: R61.1, U4.4 (Y)
RGB_DIN: J14.2, R61.2
VBUS: F1.1; also elsewhere on the board
VBUS_FUSED: C21.1, F1.2, U3.1 (VIN)
